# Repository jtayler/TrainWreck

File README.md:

# RailStation — Control Tower  
### Powered by RailOS™

> **A luxury smart power controller for any model train.**  
> RailStation replaces a “dumb” power supply with our special **control tower**. A smart control tower is a power controller with an integrated full-size traffic light; smooth motion, a large digital display, automatic station docking, and synchronized signal and lighting choreography.
> **Easy to enjoy.** Grab the knob anytime for manual override—let go and it glides back into automation. The large display changes with a click to show the list of Routes and you can scroll and pipck another Route, or click and hold a long-press to adjust settings and save them.

---

## What it does (in one minute)

- **Auto-calibrates to your layout** so station finding literally “just works.”
- Runs **scripted routes** with realistic pacing, raping speed and a human feel.
- Drives a **real traffic light** (top-and-center) + **station lights** with choreography.
- Supports **Z to G scale** by respecting a configurable power ceiling.
- The built-in series of fun Lines will run for **2–3 hours continuously** and will repeat in an endless loop.

---

## Signature features

### Smooth motion you can feel
RailOS uses non-linear ramping so starts/stops feel intentional—no lurch, no toy throttle vibe.

### Large, luxurious display
A large, elegant display turns your train into the centerpiece — with a beautifully simple interface that makes control effortless.

### Station docking that actually lands
A TINY IR sensor is used for automatic station arrival behavior: approach → crawl → stop → dwell → depart.

### Real signals, not decoration
**Traffic Light**
- **🔴 Red**: Halted / at-station
- **🟡 Yellow**: Decelerating / slow leg
- **🟢 Green**: Accelerating / fast leg

### Station lights with choreography
Four “posts” are programmable as a group:
- arrival blink patterns
- alternating pairs
- departure urgency
- slow fade-out to dark

Plus one extra output for “anything”: gate motor, windmill, sign, beacon, etc.

### Manual override that feels natural
Turn the knob → you’re in control instantly.  
Release it → after a brief pause, RailOS blends you back into the active route smoothly.

---

## Route Library (examples)
A RailStation isn’t just speed—it’s **story**. Each route has a personality:
- Pennsylvania Line
- California Zephyr
- The Orient Express
- Reading Railroad
- Flying Scotsman
- Hudson River Ltd
- 20th Century Ltd
- Taking Pelham 123  
…and more.

Routes are **editable, reorderable, deletable** and your changes **stick**.

---

## The “Human Element” controls (simple, but deep)

RailOS keeps it easy: you pick a line, and a few “human” traits shape the feel.

### Schedule (when are we running?)
- **HIGH_FREQ** — subway-like: short waits, quick turnarounds, more movement  
- **PEAK** — purposeful: brisk legs, tighter dwell times, fewer “lingers”  
- **OFF_PEAK** — relaxed: longer dwells, calmer pacing, more breathing room  

### Equipment (what kind of train is this?)
- **BULLET** — confident acceleration, longer fast legs, shorter crawls  
- **SHUTTLE** — frequent stops, shorter legs, snappy station work  
- **FREIGHT** — heavier feel: longer ramps, longer slow legs, deliberate departures  

### Service (how predictable is it?)
- **NONSTOP** — fewer station events, more continuous running  
- **LIMITED** — selective stops, “express” pacing and timing  
- **UNPREDICTABLE** — controlled variation: small changes that feel human, not random  

### Range (what kind of run is this?)
- **LOCAL** — close stations, frequent choreography, short dwell cycles  
- **SHORT_RUN** — medium legs, balanced station time  
- **LONG_HAUL** — longer cruising legs, fewer but more “cinematic” station moments  

These traits automatically influence:
- station dwell time
- leg length and speed targets
- ramp aggressiveness
- lighting choreography timing
- controlled variation (the “human element”)

---

## Scales & power
RailStation works across scales by capping output with **MAX_SPEED**:
- tiny trains (T/Z) behave safely
- large trains (O/G) still feel powerful
- same controller, different ceiling

---

## RailOS 1.0
RailOS is the C++ firmware that runs RailStation Control Tower:
- motion physics + ramp engine
- station sensor logic
- profile persistence (edits stick)
- signal + station light choreography
- continuous route runner
- manual override blending

---

## Our Motto
**Easy to enjoy.**  
**Your train. Our brain.**

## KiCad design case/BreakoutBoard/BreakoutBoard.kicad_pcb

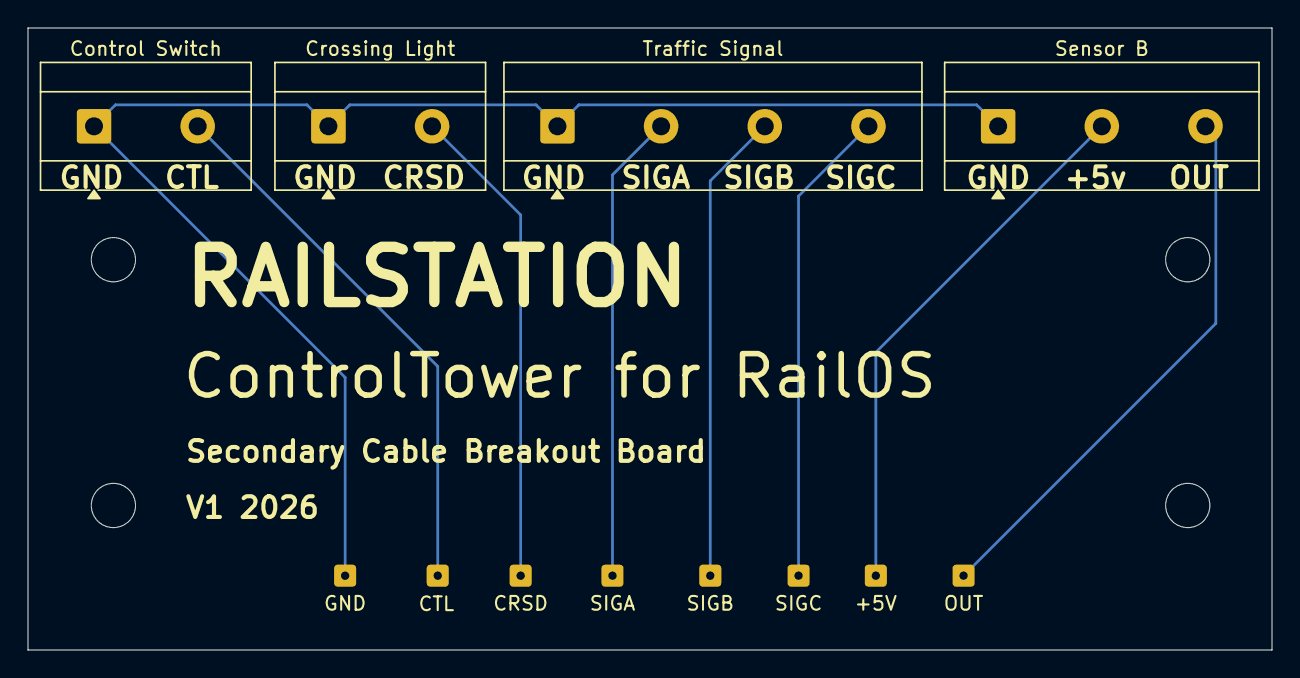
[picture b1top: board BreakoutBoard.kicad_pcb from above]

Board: 2 copper layers, 90.0 x 45.0 mm, 15 parts (0 on the bottom side), 7 nets.

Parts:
+5V: GND; SolderWire-0.1sqmm_1x01_D0.4mm_OD1mm
B.R.: MountingHole_3.2mm_M3
BottomLeft: MountingHole_3.2mm_M3
CRSD: GND; SolderWire-0.1sqmm_1x01_D0.4mm_OD1mm
Control Switch: Crossing Light; TerminalBlock_MetzConnect_Type171_RT13702HBWC_1x02_P7.50mm_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
Crossing Light: Crossing Light; TerminalBlock_MetzConnect_Type171_RT13702HBWC_1x02_P7.50mm_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
GND: GND; SolderWire-0.1sqmm_1x01_D0.4mm_OD1mm
OUT: GND; SolderWire-0.1sqmm_1x01_D0.4mm_OD1mm
SIGA: GND; SolderWire-0.1sqmm_1x01_D0.4mm_OD1mm
SIGB: GND; SolderWire-0.1sqmm_1x01_D0.4mm_OD1mm
SIGC: GND; SolderWire-0.1sqmm_1x01_D0.4mm_OD1mm
Sensor B: Sensor; TerminalBlock_MetzConnect_Type171_RT13703HBWC_1x03_P7.50mm_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
TopLeft: MountingHole_3.2mm_M3
TopRight: MountingHole_3.2mm_M3
Traffic Signal: TerminalBlock_MetzConnect_Type171_RT13704HBWC_1x0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; TerminalBlock_MetzConnect_Type171_RT13704HBWC_1x04_P7.50mm_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

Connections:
A2: SIGA.1, Traffic Signal.2
B2: SIGB.1, Traffic Signal.3
C2: SIGC.1, Traffic Signal.4
D2: CRSD.1, Crossing Light.2
GND2: Control Switch.1, Crossing Light.1, GND.1, Sensor B.1, Traffic Signal.1
OUT2: OUT.1, Sensor B.3
VCC2: +5V.1, Sensor B.2

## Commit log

2025-12-25 Initial commit: TrainWreck nano app
2025-12-25 let's adjust a few details
2025-12-26 still adjusting and testing.
2025-12-26 updates and adjustments during testing.
2026-01-10 move to a better ramp, actually use min speed
2026-01-23 clean up after wrong file situation!
2026-01-23 brush up the display reporting
2026-01-24 handle the new controller that I did not yet fry-- pass one.
2026-01-24 second pass, seems to pass test. a bit different voltage cliff seems less accurate on the spectrum, so the max speed is greatly reduced and the ramps needed adjustment to suit.
2026-01-24 more adjustments to get the reporting correctly timed for all events.
2026-01-31 first pass at making a display do something.
2026-02-06 display santity!!
2026-02-06 let's push some traffic light code and prepare
2026-02-07 fix up reporting, prep for traffic light and update details for working train! hooray!
2026-02-08 traffic light installed and wired. just waiting for the item itself...
2026-02-12 prepare for IR and try to see why this traffic light will NOT WORK!!
2026-02-14 updating speed and ramp rates to reach 10v vs 6 or less even this may improve reliability
2026-02-15 fully operational ramp and traffic light support, first pass at timer tick to land at a station but this is going well for a change-- no jinx
2026-02-15 monster update to readme anyway
2026-02-20 motor controller hell
2026-02-21 first pass new timing system and lights for the station not yet working
2026-02-22 sanity checkpoint testing
2026-02-22 ok! Sensor working! Train seems to reliably end at the station, no way - just no fucking way - this is so cool
2026-02-23 sweet adustments...
2026-02-23 trying to test the whole show!
2026-02-24 very nice details!
2026-02-24 small change
2026-02-24 good!
2026-02-24 very nice! whew!
2026-02-24 oops!
2026-02-24 ABOARD
2026-02-24 store basics to memory, perform a startup configuration. very cool whatever the train acts like forward and reverse are measured so it is accurate...
2026-02-25 crawling along with updates...
2026-02-25 still working on the details of how this should work. the train died a sad death. I may be able to return it.
2026-02-25 let's see if we can remove the delay() calls and keep those lights and display stuff active.
2026-02-25 uncertain if it's best to go directly into the next phase if we're uncertain where along the ring the trigger happens. what I likely want to do is start the blink at a pwm level or I might be already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
2026-02-26 clean up and write a readme
2026-02-26 Revise README for clarity and detail improvements
    Updated README.md to enhance descriptions and correct typos.
2026-02-26 Revise README description for RailStation
    Updated the description of RailStation for clarity and detail.
2026-02-26 Enhance README with traffic light feature
    Updated description to include integrated traffic light.
2026-02-26 add a website and a way to make the reporting on display more imaginative.
2026-02-26 fixings make it run smooth
2026-02-27 continue adjustments toward formal release candidate.
2026-02-28 adjust screen for KPH and a few things as we prepare for release
2026-03-01 new train shows patterns of changes needed to adjust the station stuff mostly --
2026-03-01 detail work around the calibration, prepare for manual control.
2026-03-01 first pass at the new knob but it's not easy to get output from it reliably -
2026-03-01 stable point charlie
2026-03-02 try to get an encoder firing from hardware interrupt
2026-03-02 the wheel and button are starting to work!!! far out!
2026-03-02 sanity checkpoint charlie
2026-03-02 most of the way to manual mode
2026-03-02 slowly--
2026-03-02 fuck man.
2026-03-02 oh yea -- working manual override
2026-03-02 sweet.
2026-03-03 a solid state of manual intervention - what a mess.
2026-03-03 let's move this into the next phase of gorgeousness!
2026-03-04 completed train configuration working again.
2026-03-04 splash screen, startup fixes and working calibration are all there now.
2026-03-04 draw some line art of the upcomging display and website along with finally smoothing out the darn thing's reverse when stopped. traffic lights work in manual etc.
2026-03-06 start building up the assets
2026-03-07 add a breakout board and connector stuff
2026-03-07 rest of it
2026-03-07 updates moving toward start of manufacture
2026-03-08 let's update!
2026-03-09 add the knob
2026-03-09 cleanup the repo a bit
2026-03-09 whatever updates
2026-03-19 adding station lights to manual control.
2026-03-22 whoa! we be outta RAM !! even after being tricky with it, the whole sketch itself is just bursting, so this is where the Nano version ends.
2026-03-30 this code is too big for the poor nano! 2.0 must be moved up in schedule.
2026-04-14 keep that updated.
2026-04-16 snooze fixes
2026-04-17 moving things around to save memory!
2026-04-28 clean up text fix up ramping and a bunch of stuff
2026-04-28 move toward that 2.0 rail os ramp and calibration. back to dual calibrate and EPROM handling.
2026-04-28 we have to account for changes to the calibration and enforce recalibration when needed.
2026-04-28 screen dirt
2026-04-29 latest updates to push
2026-04-30 divide by clock hours - work on ramp time.
2026-04-30 let's see if this works.
2026-04-30 fix it up a tad -- see about this ramp issue --
2026-05-02 clean up a few 2.0 things as we test
2026-05-06 check this in before it gets destrroyed!
2026-05-06 reliable hourly landing -finally
2026-05-07 well, 480 is holding.
2026-05-07 continue improvements.
2026-05-08 a highly reliable station docking algo--
2026-05-08 possibly more accurate IR logic --
2026-05-09 bit-o-progress and an offset that is crux perhaps.
2026-05-13 prepare to capture max speed.
2026-05-13 a few touches to details
2026-05-30 trying to stay in the RAM boundaries here.
